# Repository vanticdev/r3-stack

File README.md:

# B.L.I.T.Z

Robotics development platform, currently implementing multi-process deployment
with a Python watchdog, codegen, and deploy tooling.

See [BLITZ values](values.md) for the design principles that guide development
and prevent regressions.

## Repository layout for v1

The repository now reserves the following areas for the full-stack robotics
platform. New areas contain README placeholders only; no platform services,
schemas, simulators, or web application have been implemented yet.

```text
apps/web/                    Single future platform web application
services/orchestrator/       Project API, change coordination, validation jobs
services/simulation-worker/  Execution of simulation jobs
packages/robot-model/        Versioned robot specification and derived graph
packages/component-catalog/  Supported component descriptions and model references
packages/wiring/             Electrical connections and physical cable routing
packages/simulation/         Shared clock, simulator coordination, and results
packages/hardware-interface/ Virtual and physical hardware interface contracts
integrations/onshape/        Mechanical design import and version references
integrations/kicad/          Electronics import; provider choice remains provisional
integrations/github/         Repository references and CI workflow integration
examples/robots/             Future reproducible robot examples
docs/architecture/          Platform structure and boundaries
docs/deployment/            Existing BLITZ deployment documentation
backend/                    Existing deployment and compilation tooling
watchdog/                   Existing target-side runtime
proto/                      Existing watchdog protocol definitions
scripts/                    Existing installers and operational commands
docker/, ops/               Existing test images and system service definitions
__tests__/                  Existing deployment and runtime tests
```

The standalone marketing site has been removed. `apps/web/` is the home for the
single future site. Existing deployment commands below still use their original
paths. See the [repository layout guide](docs/architecture/repository-layout.md)
for ownership, dependency boundaries, and unresolved implementation decisions.

## Install BLITZ

Run this command on the machine you want to set up:

```bash
/bin/bash -c "$(curl -fsSL https://raw.githubusercontent.com/PinewoodRobotics/B.L.I.T.Z/HEAD/scripts/ui/install.sh)"
```

Choose **Coprocessor** to install the target watchdog, or
**Development computer** from a project directory to install the Python
deployment backend. On the development computer, choose `wpilib` integration
for a Java WPILib project; otherwise choose `none`.

For automation, set `BLITZ_INSTALL_TARGET=coprocessor` or
`BLITZ_INSTALL_TARGET=development`. The development installer also accepts
`BLITZ_SETUP=wpilib` and `BLITZ_PROJECT=/path/to/project`.

## Development backend

This installs `backend/deployment`, `backend/deploy.py`, and
`scripts/backend.sh`. The version stamp at
`backend/deployment/.blitz-build-version` identifies the backend folder: the
backend folder is the parent of `deployment/`. Reinstalling preserves your
`deploy.py`. Run `scripts/backend.sh` to deploy, check updates, add a module,
or see the detected backend location.

**Add module** asks for a name and a language (Python, Rust, or C++), creates
`backend/<language>/<name>` with a runnable sample program, and registers it in
`deploy.py`: a `ProcessType` member, a `modules.<language>(...)` declaration,
and one fleet-wide `ProcessPlan` placement. If `deploy.py` has been customized
beyond recognition, the files are still created and the declarations to add are
printed instead. For automation:
`BLITZ_BACKEND_ACTION=add-module BLITZ_MODULE_NAME=vision BLITZ_MODULE_LANGUAGE=cpp bash scripts/backend.sh`.

For a non-interactive installation into another project, set `BLITZ_PROJECT`
to its root. Set `BLITZ_BACKEND_DIR` to choose a different backend folder; the
installer adds a `backend` import alias because the Python API uses that package
name.

Discovery immediately generates one Dockerfile and build context for each
distinct discovered system ID. The Dockerfile and its build inputs are kept under
`build/backend-bundle/contexts/<system-id>/`. Its base image matches the
target distribution and architecture. The adjacent `build-plan.json` lists
every module declared by `get_modules()`, plus ordered dependency and build
steps. `build_system.sh` provisions the image in a cached Docker layer, then
executes the complete build plan after sources are copied into the image.
BLITZ extracts the resulting C++, Rust, and Python artifacts into the usual
zip bundle, including a copy of the plan, and sends the zip to the target. The
Docker image is only a build environment and is never run on the target.

```text
build/
  backend-bundle/
    contexts/<system-id>/        Dockerfile, build script, plans, staged sources
    systems.json                  saved build profiles only; no device addresses
    artifacts/<system-id>/       extracted files before packaging
    logs/<system-id>/            Docker dependency, compile, and extraction logs
    outputs/<system-id>.zip      finished bundle
    outputs/bundle-index.json    bundle checksums
```

Run one deployment command from the project root while connected to the devices:

```bash
python3 backend/deploy.py
```

This discovers watchdog endpoints through mDNS, filters blacklisted hostnames
and IP addresses, then collects each remaining watchdog's HTTP system catalog
once. It records only distinct build profiles in
`build/backend-bundle/systems.json`, refreshes the Dockerfiles and build inputs,
checks the local Docker dependency images, compiles bundles with network
access disabled, and distributes them. If matching dependency images are missing,
BLITZ checks public HTTPS services for internet access and attempts to prepare
the missing images when it is detected. Failed preparation stops deployment
before compilation or transfer. Complete caches need no internet check.

Without detected internet access, if an older dependency image for the same
system is still cached, deployment asks whether to continue with that image.
The default answer is no; continuing may leave
out new dependencies or fail compilation. If there is no cached image for a
system type, deployment stops before building or transferring bundles. To
prepare dependencies ahead of deployment, connect the build machine to the
internet and run:

```bash
python3 backend/deploy.py cache
```

The cache command uses recorded system types without contacting devices.
It is optional when internet access is available during deployment.
Reconnect to the device network and rerun `python3 backend/deploy.py`. Source
changes alone do not invalidate dependency images. Python wheels and Rust crates
are downloaded during online cache preparation; C++ dependency commands also
run there. The device never runs the Docker image and installs Python wheels
from the bundle without internet access.

Docker builds show each dependency or compilation step as it starts and ends.
Full output is saved in `build/backend-bundle/logs/<system-id>/` (including
`dependencies.log` and `compile.log`). If a step fails, the terminal reports
its phase, step, module, exit code, and log path, followed by the recent Docker
output. Set `BLITZ_VERBOSE=1` to stream every Docker output line while it runs.

The self-contained backend in `__tests__/fixtures/bundling_backend/` exercises
C++ and Rust libraries and executables. Run
`.venv/bin/python -m pytest __tests__/native_bundle_tests.py` to build its
Docker bundle, inspect the zip, and execute all four artifacts in a container.

If mDNS is unavailable, supply watchdog addresses with `--device HOST:PORT`, for
example `python3 backend/deploy.py --device 192.168.1.50:5000`. The flag is
repeatable. Known addresses enter the same blacklist and HTTP catalog collection
phase; the client requests `/get/system/catalog` from each selected watchdog.
This also supports real watchdogs running in Docker simulations.

For a saved simulation setup, fill `SIMULATION_DEVICES` with watchdog `HOST:PORT`
addresses in `backend/deploy.py`, then run `python3 backend/deploy.py --simulation`.
Simulation is off by default and bypasses mDNS completely. Containers must
already be running with those ports published.

Optional `FLEET_SIZE` and `DEVICE_PROFILES` settings in that
script check the fleet before building or transferring anything. The count is
exact; types use architecture/OS/capability profiles and require distinct devices.
Use `--expected-systems 3` for a temporary count override. See the
[configuration examples](docs/deployment/device-discovery.md#optional-fleet-expectations).

Use repeatable `--blacklist HOST_OR_IP` arguments to exclude devices before
catalog requests, building, or transfer. Blacklists match advertised hostnames
and IP addresses. Live device identities and ports are not saved as future
deployment destinations. Each deployment discovers or receives its current
targets anew.

The 3.0 discovery protocol uses `_watchdog._tcp.local.` and lightweight,
versioned mDNS metadata containing identity and service endpoints. Full system
specifications and capabilities come from the watchdog's cached HTTP catalog.
Update watchdogs and deployment tooling together. See
[device discovery and capabilities](docs/deployment/device-discovery.md) for the contract,
refresh behavior, and simulation endpoint configuration.

If a device is unavailable but its system build key is known, prepare its cache
without contacting the device:

```bash
python3 backend/deploy.py cache --system-id 2.36-aarch64-debian-12-python3-11
```

This records the profile but does not select a deployment destination. The
resulting zip bundles and checksum index are under
`build/backend-bundle/outputs/`; extracted artifacts are under
`build/backend-bundle/artifacts/`. Keep this folder and Docker's local images
when switching networks. Cross-architecture targets require Docker support
for the target platform. WPILib projects can use `deployBackend` and
`cacheBackend`; the installed `scripts/backend.sh` menu provides Deploy and
Cache dependencies. Automation can set `BLITZ_BACKEND_ACTION` to `deploy` or
`cache`.

## WPILib Java Project Setup

Choose `wpilib` integration when installing the development backend in a Java
WPILib project, or set `BLITZ_SETUP=wpilib` for automation.

WPILib setup adds the Gradle `deployBackend` task by setting `backendPath` in
`settings.gradle` or `settings.gradle.kts` and applying the task script in
`backend/deployment/gradle`. An existing backend can add this integration with
`BLITZ_BACKEND_ACTION=setup-wpilib bash scripts/backend.sh`.

Run the Gradle task with Gradle's own console output muted so BLITZ can keep
control of the terminal:

```bash
./gradlew --console=plain --quiet deployBackend
```

The previous `install_on_wpilib.sh` entry point remains available for existing
WPILib installation workflows.

## Quickstart (local)

```bash
make setup
make set-name NAME=dev
make generate
make run
```

## Tests

The default test suite includes Docker-based installation tests. Start Docker
before running tests; Docker Buildx 0.13 or newer is required.

```bash
make test
```

Docker tests use a disposable builder with its own cache volume. Installation
images are reused within a test session, and that builder's unused cache is
trimmed toward 4 GB after each build. Teardown removes the session's images,
containers, anonymous volumes, networks, and complete builder cache, including
after test failures. Successful pytest runs discard temporary bundles and build
contexts; only the latest failed session's temporary files are retained for
debugging. Active concurrent runs are protected. Cleanup errors fail the run
visibly.

This does not prune your existing shared Docker cache or deployment images.
The 4 GB target applies to unused test build cache between builds, not total
Docker disk usage or an active build's peak storage. A small reusable BuildKit
service image remains installed; build dependencies are provisioned again for
each new test session. If pytest is forcibly killed or Docker stops before
teardown, use `make test-clean` after stopping all Docker test runs to remove
leftover resources owned by this test harness.

## Deploy to a target machine

```bash
make deploy-sync
make deploy
```

### Module entrypoints, libraries, resources, and target constraints

For an existing project, follow [backend migration](docs/deployment/backend-migration.md)
to reorganize older layouts after updating BLITZ.

See [deployment architecture](docs/deployment/deployment-architecture.md) for the
deployment layout, deployment dataflow, target bundle retention, native
library linking/loading, and runtime paths and flags.

See [deployment examples](docs/deployment/deployment-examples.md) for a complete
`backend/deploy.py` template, two Python module entrypoints, Python using a C++ library,
C++/Rust executables, resources, target restrictions, and deployment commands.

All module sources live under `backend/<language>/<module-folder>`. One module
owns one complete folder; different entry files cannot be registered as separate
modules sharing that folder. Shared
Python source lives in `backend/python/common/`; sibling modules are not added
to Python import paths. Native common folders remain accessible to build files
inside the backend tree.

Keep module declarations in `get_modules()` and assign their process types in
`pi_name_to_process_types()`. Module `name` is a globally unique ID; a runnable
module's `equivalent_run_definition` supplies its process ID. These IDs may differ.
Existing positional constructors and default Python `__main__.py` entrypoints
remain supported.

```python
from backend.deployment.module.contracts import (
    CapabilityRequirement, LaunchSettings, ModuleOutputs,
    PythonEntrypoint, TargetRequirements,
)

from backend.deployment.module.catalog import BackendModules

modules = BackendModules(__file__)

# Each module owns a different folder; both use the shared requirements.
modules.python(
    "camera", process=ProcessType.CAMERA, entrypoint="camera.py",
    dependencies=("vision-library",),
    outputs=ModuleOutputs(resources=("assets/**/*",)),
    launch=LaunchSettings(arguments=("--mode", "tracking")),
)
modules.python("navigation", process=ProcessType.NAVIGATION, entrypoint="navigation.py")
```

Use `PythonEntrypoint(file=None, package="control.worker")` for `python -m`.
C++ and Rust runnable modules use `runnable_name` to select their compiled
executable. Watchdog passes argument lists directly, uses an absolute interpreter
and executable path, and sets the working directory to the bundled module folder.
`LaunchSettings.working_directory` can select a subfolder. Program paths and
arguments can contain spaces. BLITZ CLI flags are disabled by default. Legacy
programs can explicitly opt in
with `LaunchSettings(accepts_blitz_flags=True)`.
BLITZ also supplies those values through environment variables, including
`BLITZ_CONFIG_PATH`, `BLITZ_BUNDLE_FOLDER_PATH`, and `BLITZ_SYSTEM_NAME`.

Declare module dependencies by ID, for example `dependencies=("math-library",)`.
The builder rejects unknown IDs, duplicate module/process IDs, and dependency
cycles, then orders compilation across Python, C++, and Rust modules. It builds
all compatible declared modules for each profile, regardless of process assignment.
Native consumers receive `LIBRARY_PATH`, `LD_LIBRARY_PATH`, `CPATH`,
`CMAKE_LIBRARY_PATH`, `CMAKE_INCLUDE_PATH`, and Rust native search flags for their
transitive dependencies. `BLITZ_INCLUDE_DIR/<module-id>` provides an explicit,
namespaced header root. Build commands still choose which libraries to link.

`ModuleOutputs` accepts relative glob patterns:

- `libraries` and `executables` are relative to the module's bundled native build
  outputs. Unspecified library patterns export all recognized native libraries.
- `headers` and `resources` are relative to the source folder. Declared files must
  exist; missing outputs and invalid native entrypoints fail the build.
- Header exports appear under `include/<module-id>/`; library exports appear
  under `lib/<module-id>/`. Resources appear under `resources/<module-id>/` and
  retain their relative paths in the runnable module folder as well.

At runtime, `runtime-manifest.json` records each module's transitive library
search directories. Watchdog exposes `BLITZ_LIB_DIR`, `BLITZ_MODULE_DIR`, and
`BLITZ_RESOURCE_DIR`. Python receives its own module and library directories in
`PYTHONPATH`, supporting compatible Python extension modules. Shared-library
loading uses each program's dependency closure; it does not inherit the deploying
computer's library search paths. The builder checks native dependencies
recursively, packages required system libraries, and rejects unresolved libraries.
Target glibc and NVIDIA driver libraries remain supplied by the device.

Two independent programs may depend on different modules that each export
`libcommon.so`. Their library directories remain isolated. If a single dependency
closure contains different libraries with the same filename or ELF SONAME, the
build fails and names both providers; a search-path ordering cannot safely resolve
that ambiguity. Rename/relink those providers or choose one implementation.
Static `.a` libraries are compile inputs; Python `ctypes` requires a shared
library with a compatible C interface. Importable native Python extensions must
match the selected Python ABI.

Use target requirements for hardware-specific modules:

```python
from backend.deployment.compilation.util.capabilities import Capability

TargetRequirements(
    architectures=(Architecture.AARCH64,),
    capabilities=(CapabilityRequirement(Capability.CUDA, minimum_version="12.2"),),
)
```

Requirements can also restrict `distros` and exact `(major, minor)`
`python_versions`. Capabilities use the official registry in
`backend.deployment.compilation.util.capabilities`. CUDA support and NVIDIA driver
versions come from a bounded NVIDIA probe; V4L2, I²C, SPI, and GPIO report
accessible Linux device interfaces. Distribution profiles select relevant probe
families, but never imply that hardware is present. Unsupported capability names
are rejected. Custom target profiles can supply registered
`SystemId.capabilities` as `(name, value)` pairs. Capability values are part of
the profile/cache key and persist with recorded build profiles. Expensive probes
refresh periodically in the watchdog, independently of mDNS advertising.
CUDA compiler modules additionally verify the cached `nvcc` version
against the module requirement and the target driver's supported version.
Provision the appropriate toolkit using the existing C++ dependency configuration
or a supported CUDA base distro; detecting a GPU does not install a toolkit.

Incompatible modules and their consumers are skipped with the dependency chain
logged. Assigning an incompatible program fails before compilation or transfer,
including when distributing an existing bundle. The stale-dependency override
cannot bypass target compatibility checks. Dependency cache preparation stays
online; compilation stays offline. Source, entrypoint, and resource edits do not
invalidate dependency images. **All Python programs share the one root
`requirements.txt` and one target virtual environment.**

The self-contained backend in `__tests__/fixtures/module_contract_backend/`
exercises transitive libraries, exported headers, two Python modules with different entry files, conflicting library names across independent programs, and relative
resources. Run its actual Docker tests with:

```bash
.venv/bin/python -m pytest __tests__/module_contract_docker_tests.py __tests__/module_contract_tests.py
```

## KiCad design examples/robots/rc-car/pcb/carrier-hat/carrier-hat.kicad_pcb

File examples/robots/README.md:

# Robot projects

This directory is an initially empty project root for `r3 serve --projects-root examples/robots`.
Only subdirectories containing `robot.yaml` appear in the project list. This README does not create a project.

Create a project from nothing using `r3 create <name> --template blank`, then add components,
interfaces, wiring, firmware, and validation scenarios. See [build a robot](../../docs/guide/build-a-robot.md).
Keep generated meshes, recordings, caches, and build outputs out of tracked projects.
Deployable modules belong in the project’s `backend/<language>/<module-folder>` directories.

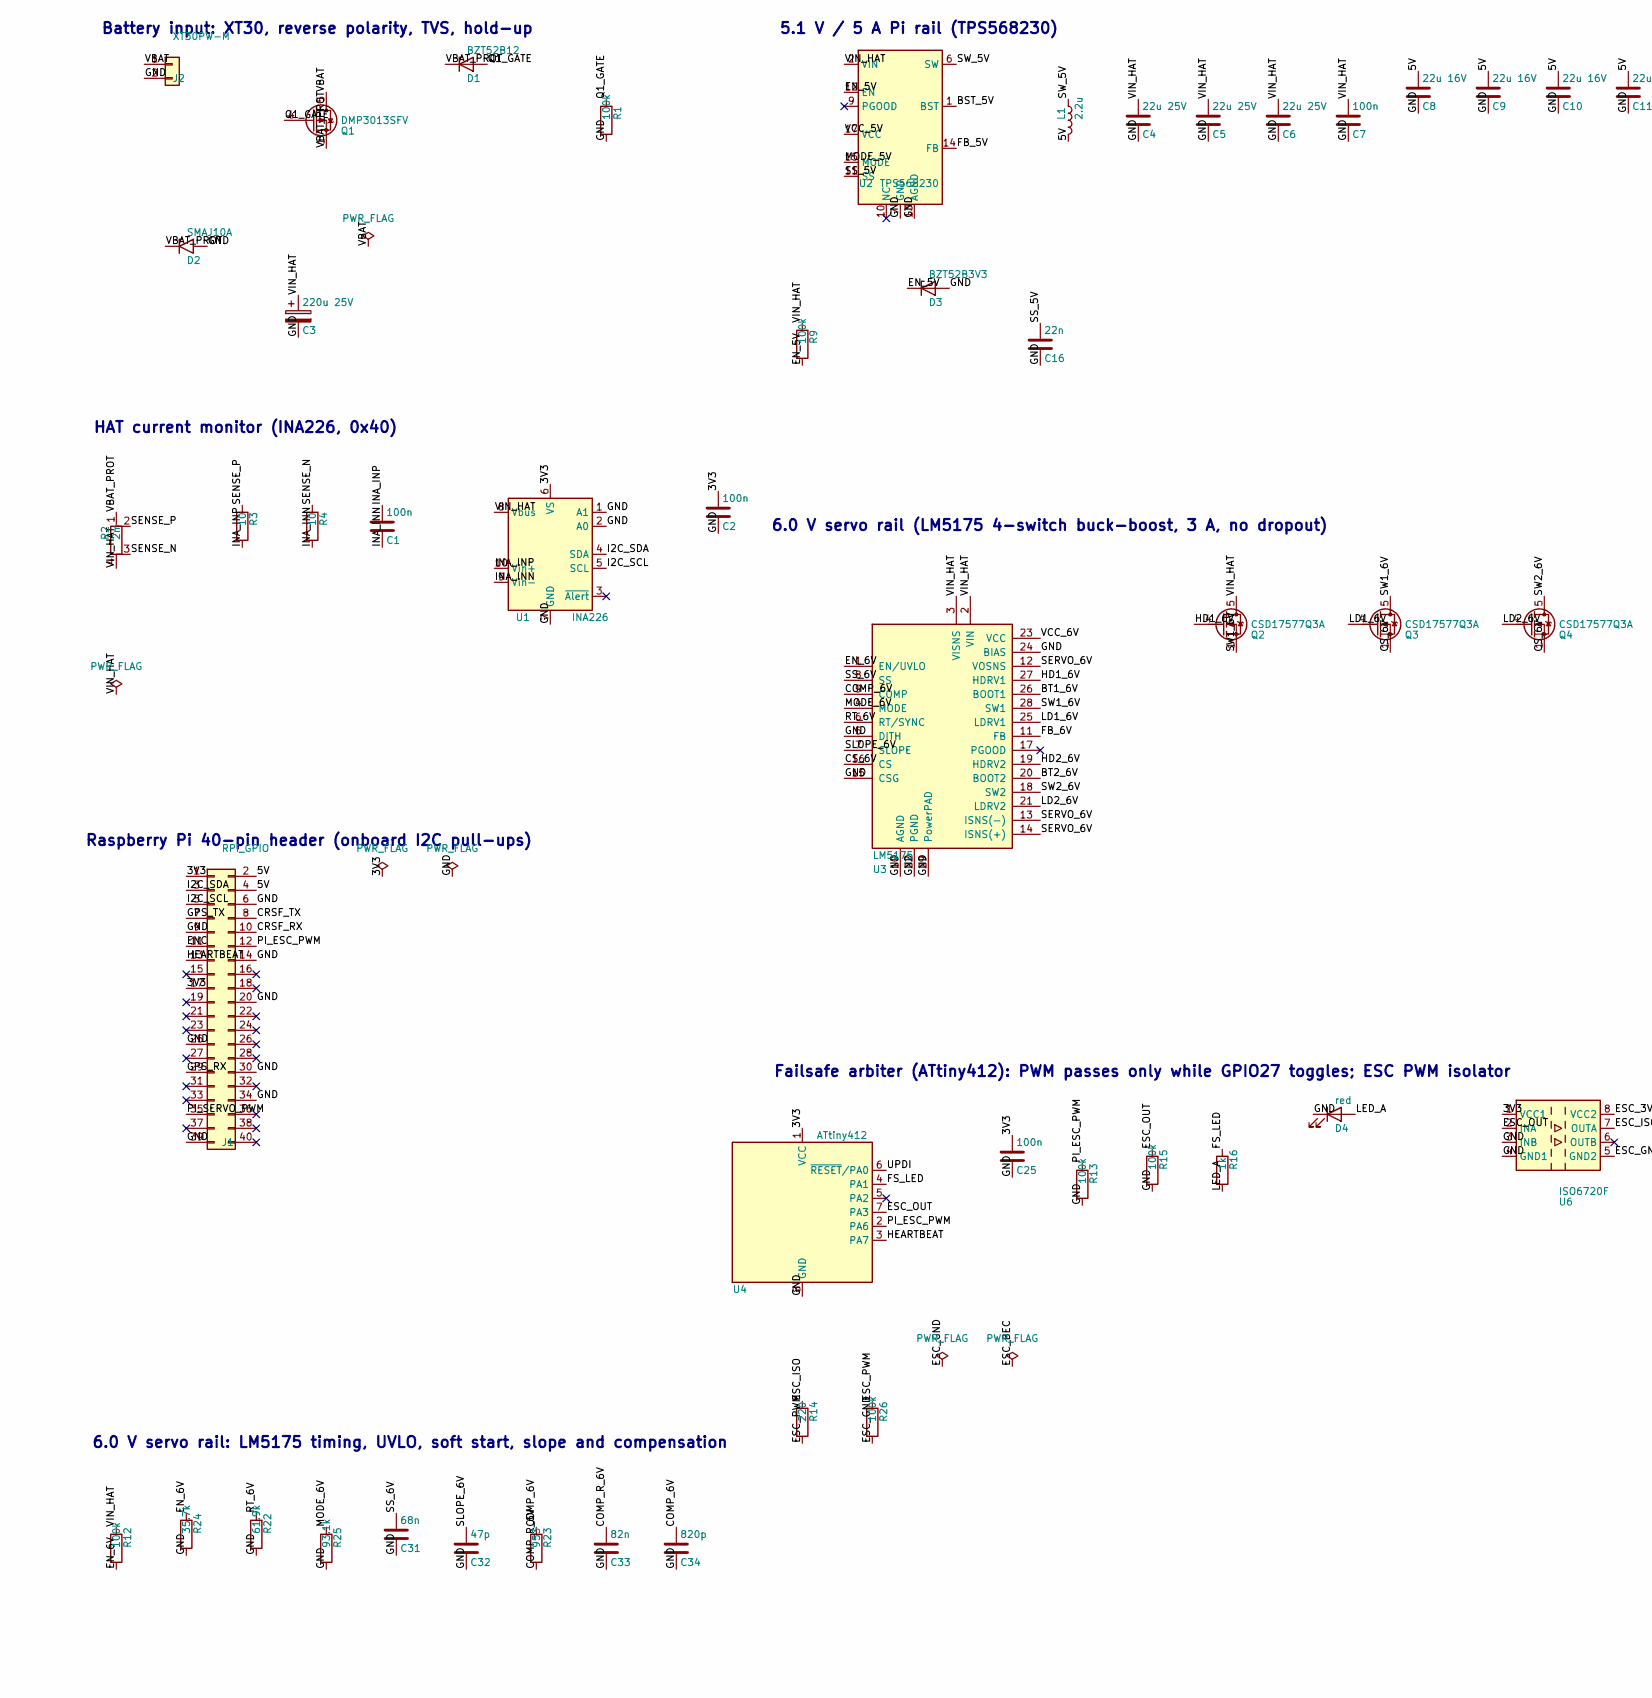
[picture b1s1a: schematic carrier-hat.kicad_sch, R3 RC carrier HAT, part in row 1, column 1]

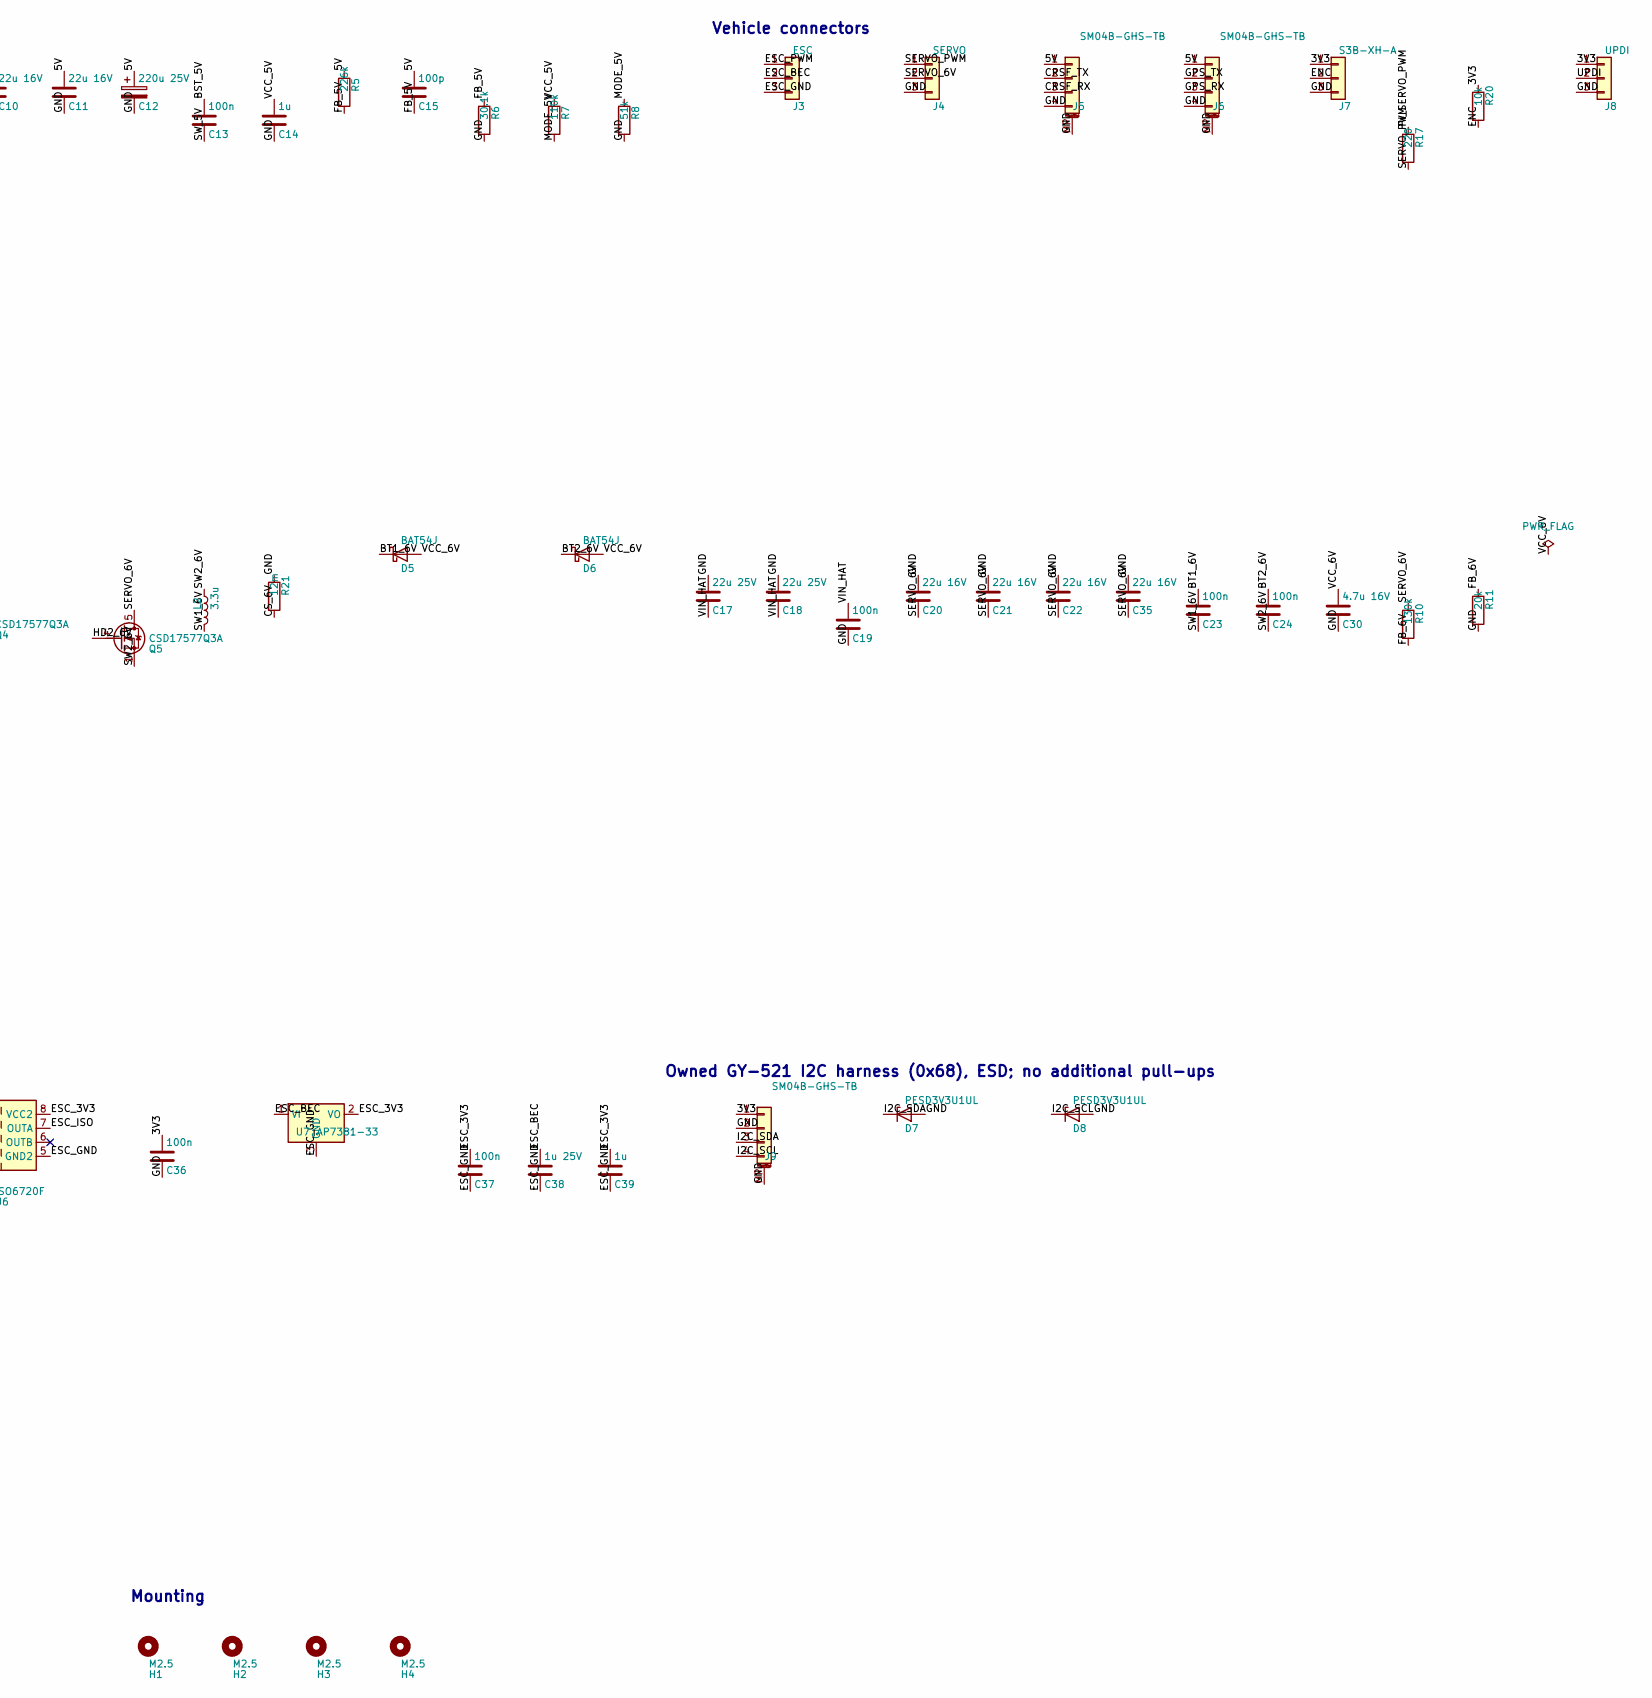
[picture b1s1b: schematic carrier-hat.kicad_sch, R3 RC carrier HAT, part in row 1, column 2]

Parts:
C1, C2, C7, C13, C25, C36, C37: 100n; C_0603_1608Metric; MPN GRM188R71H104KA93D
C3, C12: 220u 25V; CP_Elec_8x10; MPN EEH-ZA1E221P
C4, C5, C6, C17, C18: 22u 25V; C_1206_3216Metric; MPN GRM31CR61E226ME15L
C8, C9, C10, C11, C20, C21, C22, C35: 22u 16V; C_1206_3216Metric; MPN GRM31CR61C226KE15L
C14, C39: 1u; C_0603_1608Metric; MPN GRM188R61E105KA12D
C15: 100p; C_0603_1608Metric; MPN GRM1885C1H101JA01D
C16: 22n; C_0603_1608Metric; MPN GRM188R71H223KA01D
C19: 100n; C_0402_1005Metric; MPN GRM155R71H104KE14D
C23, C24: 100n; C_0402_1005Metric; MPN GRM155R71C104KA88D
C30: 4.7u 16V; C_0805_2012Metric; MPN GRM21BR61C475KA88L
C31: 68n; C_0402_1005Metric; MPN GRM155R71C683KA88D
C32: 47p; C_0402_1005Metric; MPN GRM1555C1H470JA01D
C33: 82n; C_0402_1005Metric; MPN GRM155R71C823KA88D
C34: 820p; C_0402_1005Metric; MPN GRM1555C1H821JA01D
C38: 1u 25V; C_0603_1608Metric; MPN GRM188R61E105KA12D
D1: BZT52B12; D_SOD-123F; MPN BZT52B12-7-F
D2: SMAJ10A; D_SMA; MPN SMAJ10A
D3: BZT52B3V3; D_SOD-123F; MPN BZT52B3V3-7-F
D4: red; LED_0603_1608Metric; MPN 150060RS75000
D5, D6: BAT54J; D_SOD-323F; MPN BAT54J,115
D7, D8: PESD3V3U1UL; D_SOD-882; MPN PESD3V3U1UL
H1, H2, H3, H4: M2.5; MountingHole_2.7mm_M2.5
J1: RPi_GPIO; PinSocket_2x20_P2.54mm_Vertical; MPN PPPC202LFBN-RC
J2: XT30PW-M; AMASS_XT30PW-M_1x02_P2.50mm_Horizontal; MPN XT30PW-M
J3: ESC; PinHeader_1x03_P2.54mm_Horizontal; MPN PH1-03-RA
J4: SERVO; PinHeader_1x03_P2.54mm_Horizontal; MPN PH1-03-RA
J5, J6, J9: SM04B-GHS-TB; JST_GH_SM04B-GHS-TB_1x04-1MP_P1.25mm_Horizontal; MPN SM04B-GHS-TB(LF)(SN)
J7: S3B-XH-A; JST_XH_S3B-XH-A_1x03_P2.50mm_Horizontal; MPN S3B-XH-A(LF)(SN)
J8: UPDI; PinHeader_1x03_P2.54mm_Vertical; MPN PH1-03-UA
L1: 2.2u; L_Coilcraft_XAL7030-222; MPN XAL7030-222MEB
L2: 3.3u; L_Coilcraft_XAL7030-332; MPN XAL7030-332MEB
Q1: DMP3013SFV; Diodes_PowerDI3333-8; MPN DMP3013SFV-7
Q2, Q3, Q4, Q5: CSD17577Q3A; VSON-8_3.3x3.3mm_P0.65mm_NexFET; MPN CSD17577Q3AT
R1, R9, R13, R15, R26: 100k; R_0603_1608Metric; MPN RC0603FR-07100KL
R2: 2m; R_Shunt_Vishay_WSK2512_6332Metric_T1.19mm; MPN WSK25122L000FEA
R3, R4: 10; R_0603_1608Metric; MPN RC0603FR-0710RL
R5: 226k; R_0603_1608Metric; MPN RC0603FR-07226KL
R6: 30.1k; R_0603_1608Metric; MPN RC0603FR-0730K1L
R7: 110k; R_0603_1608Metric; MPN RC0603FR-07110KL
R8: 51k; R_0603_1608Metric; MPN RC0603FR-0751KL
R10: 130k; R_0402_1005Metric; MPN RC0402FR-07130KL
R11: 20k; R_0402_1005Metric; MPN RC0402FR-0720KL
R12: 100k; R_0402_1005Metric; MPN RC0402FR-07100KL
R14, R17: 220; R_0603_1608Metric; MPN RC0603FR-07220RL
R16: 1k; R_0603_1608Metric; MPN RC0603FR-071KL
R20: 10k; R_0603_1608Metric; MPN RC0603FR-0710KL
R21: 12m; R_2010_5025Metric; MPN WSL2010R0120FEA
R22: 61.9k; R_0402_1005Metric; MPN RC0402FR-0761K9L
R23: 953; R_0402_1005Metric; MPN RC0402FR-07953RL
R24: 35.7k; R_0402_1005Metric; MPN RC0402FR-0735K7L
R25: 93.1k; R_0402_1005Metric; MPN RC0402FR-0793K1L
U1: INA226; TSSOP-10_3x3mm_P0.5mm; MPN INA226AIDGSR
U2: TPS568230; Texas_RJE0020A_VQFN-20-1EP_3x3mm_P0.45mm_EP0.675x0.76mm; MPN TPS568230RJER
U3: LM5175; HTSSOP-28-1EP_4.4x9.7mm_P0.65mm_EP3.4x9.5mm; MPN LM5175PWPR
U4: ATtiny412; SOIC-8_3.9x4.9mm_P1.27mm; MPN ATTINY412-SSN
U6: ISO6720F; SOIC-8_3.9x4.9mm_P1.27mm; MPN ISO6720FBDR
U7: AP7381-33; SOT-23; MPN AP7381-33SA-7

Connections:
/3V3: C2.1, C25.1, C36.1, J1.1, J1.17, J7.1, J8.1, J9.1, R20.1, U1.6 (VS), U4.1 (VCC), U6.1 (VCC1)
/5V: C8.1, C9.1, C10.1, C11.1, C12.1, C15.1, J1.2, J1.4, J5.1, J6.1, L1.2, R5.1
/BST_5V: C13.1, U2.1 (BST)
/BT1_6V: C23.1, D5.1 (K), U3.26 (BOOT1)
/BT2_6V: C24.1, D6.1 (K), U3.20 (BOOT2)
/COMP_6V: C34.1, R23.1, U3.9 (COMP)
/COMP_R_6V: C33.1, R23.2
/CRSF_RX: J1.10, J5.3
/CRSF_TX: J1.8, J5.2
/CS_6V: Q3.1 (S), Q3.2 (S), Q3.3 (S), Q4.1 (S), Q4.2 (S), Q4.3 (S), R21.2, U3.16 (CS)
/ENC: J1.11, J7.2, R20.2
/EN_5V: D3.1 (K), R9.2, U2.12 (EN)
/EN_6V: R12.2, R24.1, U3.1 (EN/UVLO)
/ESC_3V3: C37.1, C39.1, U6.8 (VCC2), U7.2 (VO)
/ESC_BEC: C38.1, J3.2, U7.1 (VI)
/ESC_GND: C37.2, C38.2, C39.2, J3.3, R26.2, U6.5 (GND2), U7.3 (GND)
/ESC_ISO: R14.1, U6.7 (OUTA)
/ESC_OUT: R15.1, U4.7 (PA3), U6.2 (INA)
/ESC_PWM: J3.1, R14.2, R26.1
/FB_5V: C15.2, R5.2, R6.1, U2.14 (FB)
/FB_6V: R10.2, R11.1, U3.11 (FB)
/FS_LED: R16.1, U4.4 (PA1)
/GND: C2.2, C3.2, C4.2, C5.2, C6.2, C7.2, C8.2, C9.2, C10.2, C11.2, C12.2, C14.2, C16.2, C17.1, C18.1, C19.2, C20.1, C21.1, C22.1, C25.2, C30.2, C31.2, C32.2, C33.2, C34.2, C35.1, C36.2, D2.2 (A2), D3.2 (A), D4.1 (K), D7.2 (A), D8.2 (A), J1.6, J1.9, J1.14, J1.20, J1.25, J1.30, J1.34, J1.39, J2.2, J4.3, J5.4, J5.MP (MountPin), J6.4, J6.MP (MountPin), J7.3, J8.3, J9.2, J9.MP (MountPin), R1.2, R6.2, R8.2, R11.2, R13.2, R15.2, R21.1, R22.2, R24.2, R25.2, U1.1 (A1), U1.2 (A0), U1.7 (GND), U2.7 (GND), U2.8 (GND), U2.13 (AGND), U2.18 (GND), U2.21 (GND), U3.5 (DITH), U3.10 (AGND), U3.15 (CSG), U3.22 (PGND), U3.24 (BIAS), U3.29 (PowerPAD), U4.8 (GND), U6.3 (INB), U6.4 (GND1)
/GPS_RX: J1.29, J6.3
/GPS_TX: J1.7, J6.2
/HD1_6V: Q2.4 (G), U3.27 (HDRV1)
/HD2_6V: Q5.4 (G), U3.19 (HDRV2)
/HEARTBEAT: J1.13, U4.3 (PA7)
/I2C_SCL: D8.1 (K), J1.5, J9.4, U1.5 (SCL)
/I2C_SDA: D7.1 (K), J1.3, J9.3, U1.4 (SDA)
/INA_INN: C1.2, R4.2, U1.9 (Vin-)
/INA_INP: C1.1, R3.2, U1.10 (Vin+)
/LD1_6V: Q3.4 (G), U3.25 (LDRV1)
/LD2_6V: Q4.4 (G), U3.21 (LDRV2)
/LED_A: D4.2 (A), R16.2
/MODE_5V: R7.2, R8.1, U2.15 (MODE)
/MODE_6V: R25.1, U3.4 (MODE)
/PI_ESC_PWM: J1.12, R13.1, U4.2 (PA6)
/PI_SERVO_PWM: J1.35, R17.1
/Q1_GATE: D1.2 (A), Q1.4 (G), R1.1
/RT_6V: R22.1, U3.6 (RT/SYNC)
/SENSE_N: R2.3, R4.1
/SENSE_P: R2.2, R3.1
/SERVO_6V: C20.2, C21.2, C22.2, C35.2, J4.2, Q5.5 (D), R10.1, U3.12 (VOSNS), U3.13 (ISNS(-)), U3.14 (ISNS(+))
/SERVO_PWM: J4.1, R17.2
/SLOPE_6V: C32.1, U3.7 (SLOPE)
/SS_5V: C16.1, U2.11 (SS)
/SS_6V: C31.1, U3.8 (SS)
/SW1_6V: C23.2, L2.2, Q2.1 (S), Q2.2 (S), Q2.3 (S), Q3.5 (D), U3.28 (SW1)
/SW2_6V: C24.2, L2.1, Q4.5 (D), Q5.1 (S), Q5.2 (S), Q5.3 (S), U3.18 (SW2)
/SW_5V: C13.2, L1.1, U2.6 (SW), U2.19 (SW), U2.20 (SW)
/UPDI: J8.2, U4.6 (~RESET/PA0)
/VBAT: J2.1, Q1.5 (D)
/VBAT_PROT: D1.1 (K), D2.1 (A1), Q1.1 (S), Q1.2 (S), Q1.3 (S), R2.1
/VCC_5V: C14.1, R7.1, U2.17 (VCC)
/VCC_6V: C30.1, D5.2 (A), D6.2 (A), U3.23 (VCC)
/VIN_HAT: C3.1, C4.1, C5.1, C6.1, C7.1, C17.2, C18.2, C19.1, Q2.5 (D), R2.4, R9.1, R12.1, U1.8 (Vbus), U2.2 (VIN), U2.3 (VIN), U2.4 (VIN), U2.5 (VIN), U3.2 (VIN), U3.3 (VISNS)

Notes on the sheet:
HAT current monitor (INA226, 0x40)
5.1 V / 5 A Pi rail (TPS568230)
Owned GY-521 I2C harness (0x68), ESD; no additional pull-ups
Battery input: XT30, reverse polarity, TVS, hold-up
Mounting
Failsafe arbiter (ATtiny412): PWM passes only while GPIO27 toggles; ESC PWM isolator
Vehicle connectors
6.0 V servo rail (LM5175 4-switch buck-boost, 3 A, no dropout)
6.0 V servo rail: LM5175 timing, UVLO, soft start, slope and compensation
Raspberry Pi 40-pin header (onboard I2C pull-ups)

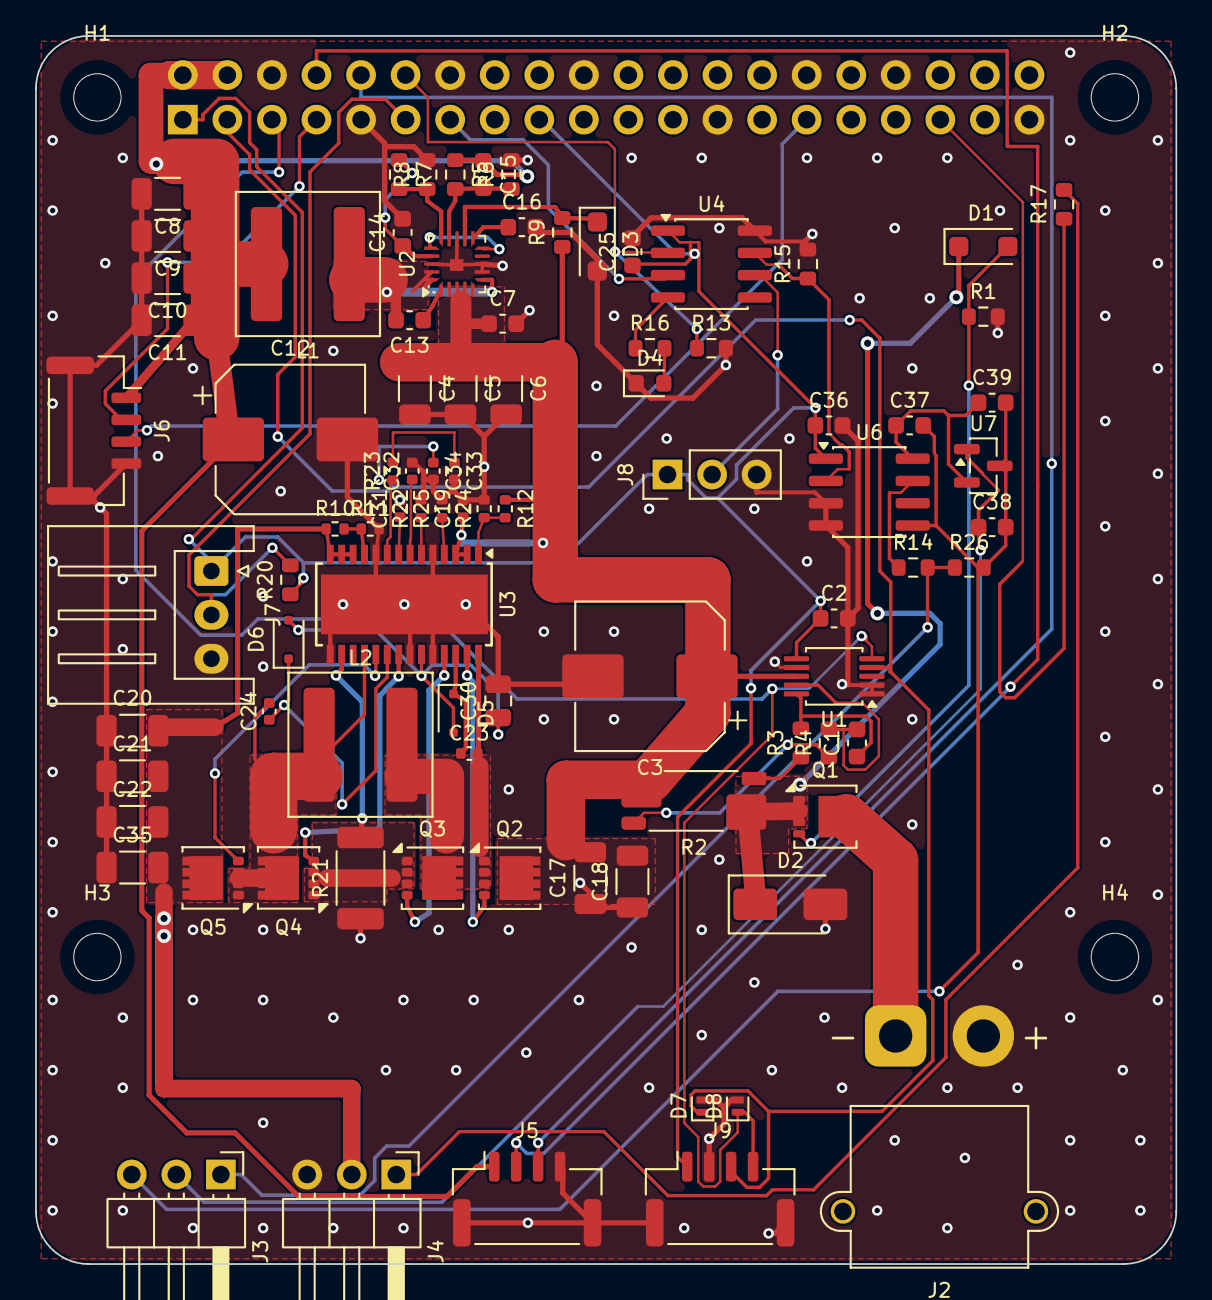
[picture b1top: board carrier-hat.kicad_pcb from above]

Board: 2 copper layers, 65.0 x 70.0 mm, 93 parts (1 on the bottom side), 57 nets.
